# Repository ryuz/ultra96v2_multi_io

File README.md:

# Ultra96V2用マルチI/O拡張カード

現在デバッグ中ですが、MIPI-CSI の動作確認できました。

## 開発イメージ

下記のようなイメージで開発している [Ultra96V2](https://www.avnet.com/wps/portal/japan/products/product-highlights/ultra96/) 向けのI/O拡張ボードです。

## 設計コンセプト

コンセプトは

- [FusionPCB](https://www.fusionpcb.jp)さんの$4.9基板で作る
- [ZYBO](https://reference.digilentinc.com/reference/programmable-logic/zybo-z7/start) の良さ(PLのI/O機能の充実)の追加
- [Raspberry PI](https://ja.wikipedia.org/wiki/Raspberry_Pi) の良さ(PSのI/O機能の充実)の追加
- 使いたい機能だけ部品実装すれば最低限のコストで使える

です。

## 機能

主な機能として

- PLの機能
    - TXS0108で3.3V双方向変換した12pin PMOD × 2個
    - RaspberryPI互換 MIPI-CSIコネクタ× 2個
    - LED × 4個
    - プッシュスイッチ × 2個 
    - ディップスイッチ(4bit) × 1個 
    - 25MHzクロック供給
- PSの機能
    - LED × 2個
    - TXS0108で3.3V双方向変換したGPIO
    - TXS0108で3.3V双方向変換したI2C
    - TXS0108で3.3V双方向変換したSPI
- その他の機能
    - 隠れると困るPWR/RSTスイッチの引き出し
    - 申し訳程度にUSB2.0信号を引き出したピンヘッダ

特に MIPI-CSI は、[こちら](http://nahitafu.cocolog-nifty.com/nahitafu/2008/11/post-57a1.html)を参考にさせて頂いて、基板厚 0.6mm の想定で設計時の机上計算のみ行っています)。

## 回路図

回路図は[こちら](documents/ultra96v2_multi_io_schematic.pdf)

## 追加情報

こちらに[ブログ記事](https://ryuz.hatenablog.com/entry/2020/07/26/215500)を書きました。

## 修正履歴

- Rev.1 2020/02/11
   - 修正内容
       - 初版
   - 動作状況
       - MIPI-CSI が同パターンの別基板でデータ受信でき無かったため、部品温存で試さずに Rev.2 製造へ

- Rev.2 2020/03/08
   - 修正内容
       - MIPI 配線レイアウト変更
       - 基板厚を 0.6mm に変更して発注
   - 動作状況
       - J3のMIPI-CSI動作確認(I2Cプルアップをリワーク修正)
       - J4のMIPI-CSI動作確認(I2Cプルアップをリワーク修正)
       - PMODの出力パルス波形確認
       - SW5(DIP-SW)の型番とフットプリントが不一致で実装できず
       - MIPI-DSIの端子をLVCMOS利用箇所でLVCMOS18と勘違いしておりLED点灯が暗い(実際はLVCMOS12)
       - 他はこれから試す予定

- Rev.3 2023/02/15
   - MIPI-CSI用 I2C プルアップ抵抗抜け修正(R23～26追加)
   - LS_GPIO_2 と LS_GPIO_6 の U4 への接続をスワップ
   - Q1-4 の DMN63D8LDW-7 -> DMN5L0-6DWK7 に変更(LVCMOS12対応)
   - SW5 の GDH04S04 のフットプリントが A6H-4101 用になっていたので両対応パターンに変更
   - fumi氏に HSコネクタに来ている信号のうち Bank65 に繋がるものがは 1.2V だと指摘頂き下記を修正
       - SW1, SW2, SW5 を FPGA内部PULLUPして論理逆で使う方針に変更(R35, R36, R31, R32, R33, R34 削除)
       - U3 を使わずにそのままピンヘッダへ (U3, C8, C10, R11, R12 削除)
       - KiCAD を 7.0.0 へ更新

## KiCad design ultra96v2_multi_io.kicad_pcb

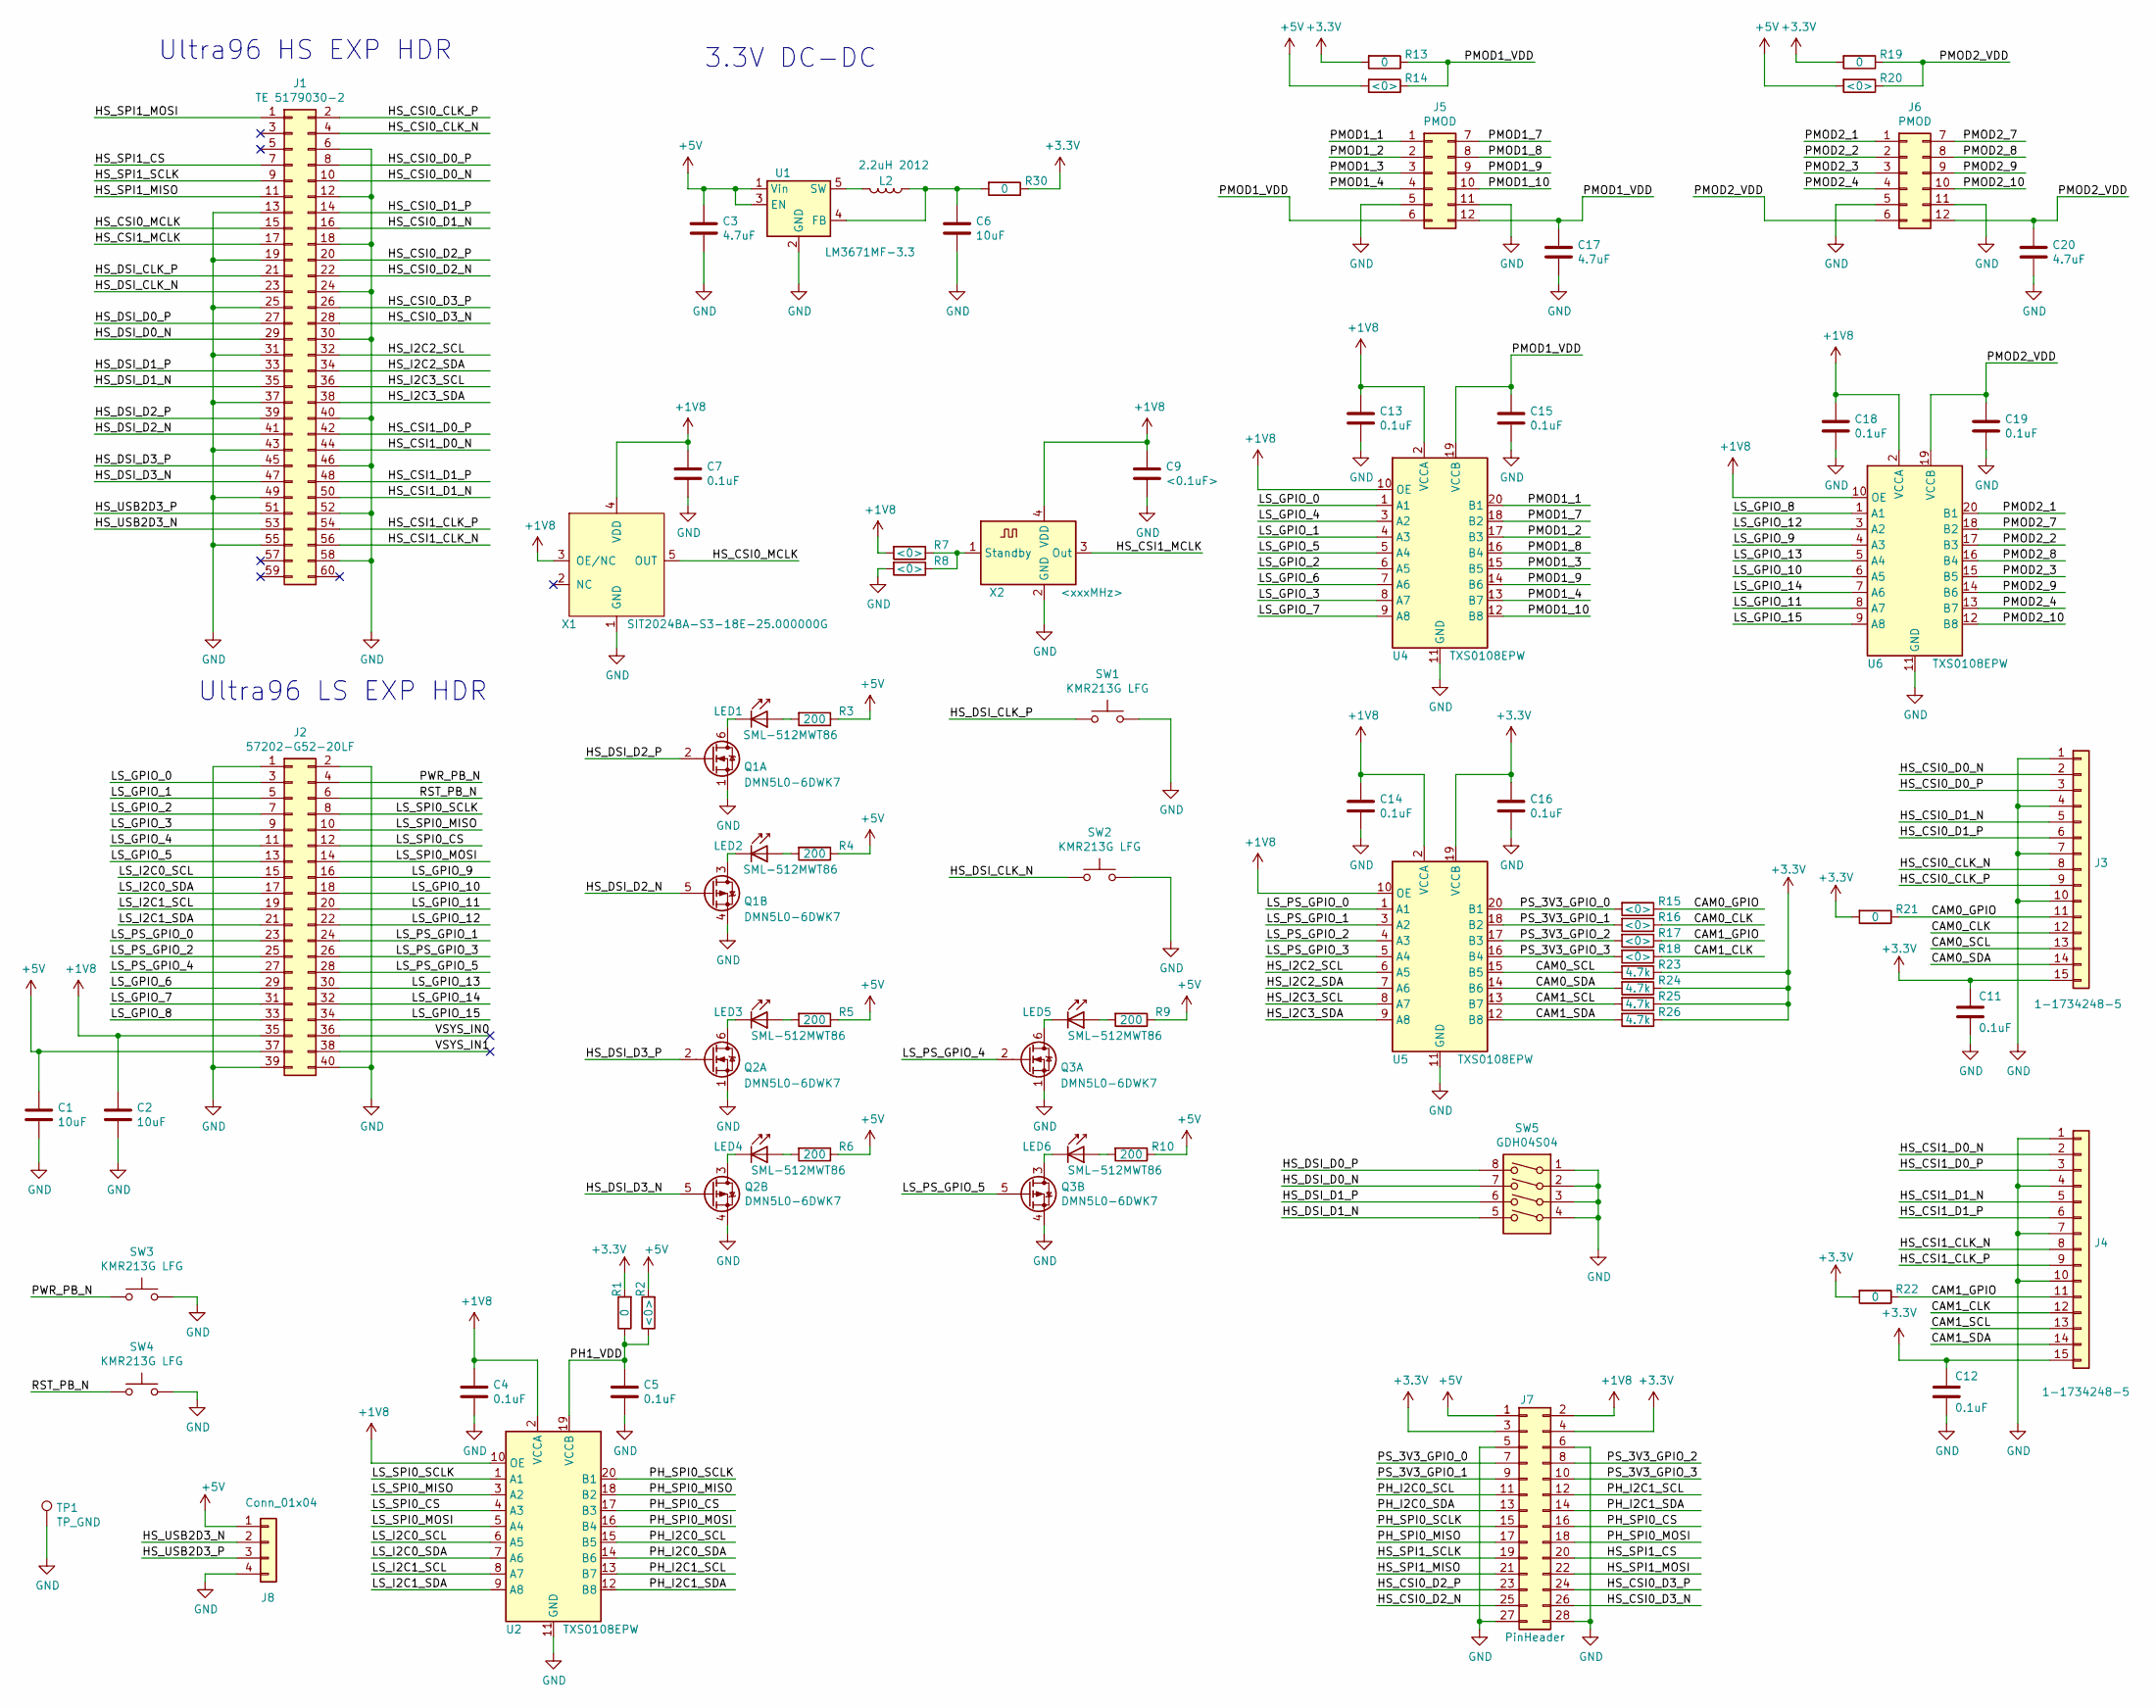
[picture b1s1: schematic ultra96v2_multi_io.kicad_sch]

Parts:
C1, C2, C6: 10uF; C_0603_1608Metric_Pad1.05x0.95mm_HandSolder
C3, C17, C20: 4.7uF; C_0603_1608Metric_Pad1.05x0.95mm_HandSolder
C4, C5, C7, C11, C12, C13, C14, C15, C16, C18, C19: 0.1uF; C_0603_1608Metric_Pad1.05x0.95mm_HandSolder
C9: <0.1uF>; C_0603_1608Metric_Pad1.05x0.95mm_HandSolder
J1: TE 5179030-2; 61083-063402LF
J2: 57202-G52-20LF; PinHeader_2x20_P2.00mm_Vertical_SMD_REV
J3, J4: 1-1734248-5; 55510-140LF_handsolder
J5, J6: PMOD; PMOD_Master
J7: PinHeader; PinHeader_2x14_P2.54mm_Vertical
J8: Conn_01x04; PinHeader_1x04_P2.54mm_Vertical
L2: 2.2uH 2012; L_0805_2012Metric
LED1, LED2, LED3, LED4, LED5, LED6: SML-512MWT86; LED_0603_1608Metric_Pad1.05x0.95mm_HandSolder
Q1, Q2, Q3: DMN5L0-6DWK7; SOT-363_SC-70-6_Handsoldering
R1, R13, R19, R21, R22, R30: 0; R_0603_1608Metric
R2, R7, R8, R14, R15, R16, R17, R18, R20: <0>; R_0603_1608Metric
R3, R4, R5, R6, R9, R10: 200; R_0603_1608Metric
R23, R24, R25, R26: 4.7k; R_0603_1608Metric
SW1, SW2, SW3, SW4: KMR213G LFG; SW_Push_1P1T_NO_CK_KMR2
SW5: GDH04S04; SW_DIP_multi_io
TP1: TP_GND; TestPoint_Loop_D1.80mm_Drill1.0mm_Beaded
U1: LM3671MF-3.3; TSOT-23-5
U2, U4, U5, U6: TXS0108EPW; TSSOP-20_4.4x6.5mm_P0.65mm
X1: SIT2024BA-S3-18E-25.000000G; SOT-23-5_HandSoldering
X2: <xxxMHz>; Oscillator_SMD_Abracon_ASDMB-4Pin_2.5x2.0mm

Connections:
+1V8: C2.1, C4.1, C7.1, C9.1, C13.1, C14.1, C18.1, J2.35, J7.2, R7.2, U2.2 (VCCA), U2.10 (OE), U4.2 (VCCA), U4.10 (OE), U5.2 (VCCA), U5.10 (OE), U6.2 (VCCA), U6.10 (OE), X1.3 (OE/NC), X1.4 (VDD), X2.4 (VDD)
+3V3: C11.1, C12.1, C16.1, J3.15, J4.15, J7.3, J7.4, R1.2, R13.2, R19.2, R21.2, R22.2, R23.1, R24.1, R25.1, R26.1, R30.1, U5.19 (VCCB)
+5V: C1.1, C3.1, J2.37, J7.1, J8.1, R2.2, R3.1, R4.1, R5.1, R6.1, R9.1, R10.1, R14.2, R20.2, U1.1 (Vin), U1.3 (EN)
/CAM0_CLK: J3.12, R16.1
/CAM0_GPIO: J3.11, R15.1, R21.1
/CAM0_SCL: J3.13, R23.2, U5.15 (B5)
/CAM0_SDA: J3.14, R24.2, U5.14 (B6)
/CAM1_CLK: J4.12, R18.1
/CAM1_GPIO: J4.11, R17.1, R22.1
/CAM1_SCL: J4.13, R25.2, U5.13 (B7)
/CAM1_SDA: J4.14, R26.2, U5.12 (B8)
/HS_CSI0_CLK_N: J1.4, J3.8
/HS_CSI0_CLK_P: J1.2, J3.9
/HS_CSI0_D0_N: J1.10, J3.2
/HS_CSI0_D0_P: J1.8, J3.3
/HS_CSI0_D1_N: J1.16, J3.5
/HS_CSI0_D1_P: J1.14, J3.6
/HS_CSI0_D2_N: J1.22, J7.25
/HS_CSI0_D2_P: J1.20, J7.23
/HS_CSI0_D3_N: J1.28, J7.26
/HS_CSI0_D3_P: J1.26, J7.24
/HS_CSI0_MCLK: J1.15, X1.5 (OUT)
/HS_CSI1_CLK_N: J1.56, J4.8
/HS_CSI1_CLK_P: J1.54, J4.9
/HS_CSI1_D0_N: J1.44, J4.2
/HS_CSI1_D0_P: J1.42, J4.3
/HS_CSI1_D1_N: J1.50, J4.5
/HS_CSI1_D1_P: J1.48, J4.6
/HS_CSI1_MCLK: J1.17, X2.3 (Out)
/HS_DSI_CLK_N: J1.23, SW2.1
/HS_DSI_CLK_P: J1.21, SW1.1
/HS_DSI_D0_N: J1.29, SW5.7
/HS_DSI_D0_P: J1.27, SW5.8
/HS_DSI_D1_N: J1.35, SW5.5
/HS_DSI_D1_P: J1.33, SW5.6
/HS_DSI_D2_N: J1.41, Q1.5 (G2)
/HS_DSI_D2_P: J1.39, Q1.2 (G1)
/HS_DSI_D3_N: J1.47, Q2.5 (G2)
/HS_DSI_D3_P: J1.45, Q2.2 (G1)
/HS_I2C2_SCL: J1.32, U5.6 (A5)
/HS_I2C2_SDA: J1.34, U5.7 (A6)
/HS_I2C3_SCL: J1.36, U5.8 (A7)
/HS_I2C3_SDA: J1.38, U5.9 (A8)
/HS_SPI1_CS: J1.7, J7.20
/HS_SPI1_MISO: J1.11, J7.21
/HS_SPI1_MOSI: J1.1, J7.22
/HS_SPI1_SCLK: J1.9, J7.19
/HS_USB2D3_N: J1.53, J8.2
/HS_USB2D3_P: J1.51, J8.3
/LS_GPIO_0: J2.3, U4.1 (A1)
/LS_GPIO_1: J2.5, U4.4 (A3)
/LS_GPIO_2: J2.7, U4.6 (A5)
/LS_GPIO_3: J2.9, U4.8 (A7)
/LS_GPIO_4: J2.11, U4.3 (A2)
/LS_GPIO_5: J2.13, U4.5 (A4)
/LS_GPIO_6: J2.29, U4.7 (A6)
/LS_GPIO_7: J2.31, U4.9 (A8)
/LS_GPIO_8: J2.33, U6.1 (A1)
/LS_GPIO_9: J2.16, U6.4 (A3)
/LS_GPIO_10: J2.18, U6.6 (A5)
/LS_GPIO_11: J2.20, U6.8 (A7)
/LS_GPIO_12: J2.22, U6.3 (A2)
/LS_GPIO_13: J2.30, U6.5 (A4)
/LS_GPIO_14: J2.32, U6.7 (A6)
/LS_GPIO_15: J2.34, U6.9 (A8)
/LS_I2C0_SCL: J2.15, U2.6 (A5)
/LS_I2C0_SDA: J2.17, U2.7 (A6)
/LS_I2C1_SCL: J2.19, U2.8 (A7)
/LS_I2C1_SDA: J2.21, U2.9 (A8)
/LS_PS_GPIO_0: J2.23, U5.1 (A1)
/LS_PS_GPIO_1: J2.24, U5.3 (A2)
/LS_PS_GPIO_2: J2.25, U5.4 (A3)
/LS_PS_GPIO_3: J2.26, U5.5 (A4)
/LS_PS_GPIO_4: J2.27, Q3.2 (G1)
/LS_PS_GPIO_5: J2.28, Q3.5 (G2)
/LS_SPI0_CS: J2.12, U2.4 (A3)
/LS_SPI0_MISO: J2.10, U2.3 (A2)
/LS_SPI0_MOSI: J2.14, U2.5 (A4)
/LS_SPI0_SCLK: J2.8, U2.1 (A1)
/PH1_VDD: C5.1, R1.1, R2.1, U2.19 (VCCB)
/PH_I2C0_SCL: J7.11, U2.15 (B5)
/PH_I2C0_SDA: J7.13, U2.14 (B6)
/PH_I2C1_SCL: J7.12, U2.13 (B7)
/PH_I2C1_SDA: J7.14, U2.12 (B8)
/PH_SPI0_CS: J7.16, U2.17 (B3)
/PH_SPI0_MISO: J7.17, U2.18 (B2)
/PH_SPI0_MOSI: J7.18, U2.16 (B4)
/PH_SPI0_SCLK: J7.15, U2.20 (B1)
/PMOD1_1: J5.1, U4.20 (B1)
/PMOD1_2: J5.2, U4.17 (B3)
/PMOD1_3: J5.3, U4.15 (B5)
/PMOD1_4: J5.4, U4.13 (B7)
/PMOD1_7: J5.7, U4.18 (B2)
/PMOD1_8: J5.8, U4.16 (B4)
/PMOD1_9: J5.9, U4.14 (B6)
/PMOD1_10: J5.10, U4.12 (B8)
/PMOD1_VDD: C15.1, C17.1, J5.6, J5.12, R13.1, R14.1, U4.19 (VCCB)
/PMOD2_1: J6.1, U6.20 (B1)
/PMOD2_2: J6.2, U6.17 (B3)
/PMOD2_3: J6.3, U6.15 (B5)
/PMOD2_4: J6.4, U6.13 (B7)
/PMOD2_7: J6.7, U6.18 (B2)
/PMOD2_8: J6.8, U6.16 (B4)
/PMOD2_9: J6.9, U6.14 (B6)
/PMOD2_10: J6.10, U6.12 (B8)
/PMOD2_VDD: C19.1, C20.1, J6.6, J6.12, R19.1, R20.1, U6.19 (VCCB)
/PS_3V3_GPIO_0: J7.7, R15.2, U5.20 (B1)
/PS_3V3_GPIO_1: J7.9, R16.2, U5.18 (B2)
/PS_3V3_GPIO_2: J7.8, R17.2, U5.17 (B3)
/PS_3V3_GPIO_3: J7.10, R18.2, U5.16 (B4)
/PWR_PB_N: J2.4, SW3.1
/RST_PB_N: J2.6, SW4.1
/VSYS_IN0: J2.36
/VSYS_IN1: J2.38
GND: C1.2, C2.2, C3.2, C4.2, C5.2, C6.2, C7.2, C9.2, C11.2, C12.2, C13.2, C14.2, C15.2, C16.2, C17.2, C18.2, C19.2, C20.2, J1.6, J1.12, J1.13, J1.18, J1.19, J1.24, J1.25, J1.30, J1.31, J1.37, J1.40, J1.43, J1.46, J1.49, J1.52, J1.55, J1.58, J2.1, J2.2, J2.39, J2.40, J3.1, J3.4, J3.7, J3.10, J4.1, J4.4, J4.7, J4.10, J5.5, J5.11, J6.5, J6.11, J7.5, J7.6, J7.27, J7.28, J8.4, Q1.1 (S1), Q1.4 (S2), Q2.1 (S1), Q2.4 (S2), Q3.1 (S1), Q3.4 (S2), R8.2, SW1.2, SW2.2, SW3.2, SW4.2, SW5.1, SW5.2, SW5.3, SW5.4, TP1.1, U1.2 (GND), U2.11 (GND), U4.11 (GND), U5.11 (GND), U6.11 (GND), X1.1 (GND), X2.2 (GND)
unnamed: LED1.2 (A), R3.2
unnamed: LED1.1 (K), Q1.6 (D1)
unnamed: LED2.2 (A), R4.2
unnamed: LED2.1 (K), Q1.3 (D2)
unnamed: LED3.2 (A), R5.2
unnamed: LED3.1 (K), Q2.6 (D1)
unnamed: LED4.2 (A), R6.2
unnamed: LED4.1 (K), Q2.3 (D2)
unnamed: LED5.2 (A), R9.2
unnamed: LED5.1 (K), Q3.6 (D1)
unnamed: LED6.2 (A), R10.2
unnamed: LED6.1 (K), Q3.3 (D2)
unnamed: C6.1, L2.1, R30.2, U1.4 (FB)
unnamed: L2.2, U1.5 (SW)
unnamed: R7.1, R8.1, X2.1 (Standby)

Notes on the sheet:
Ultra96 LS EXP HDR
3.3V DC-DC
Ultra96 HS EXP HDR

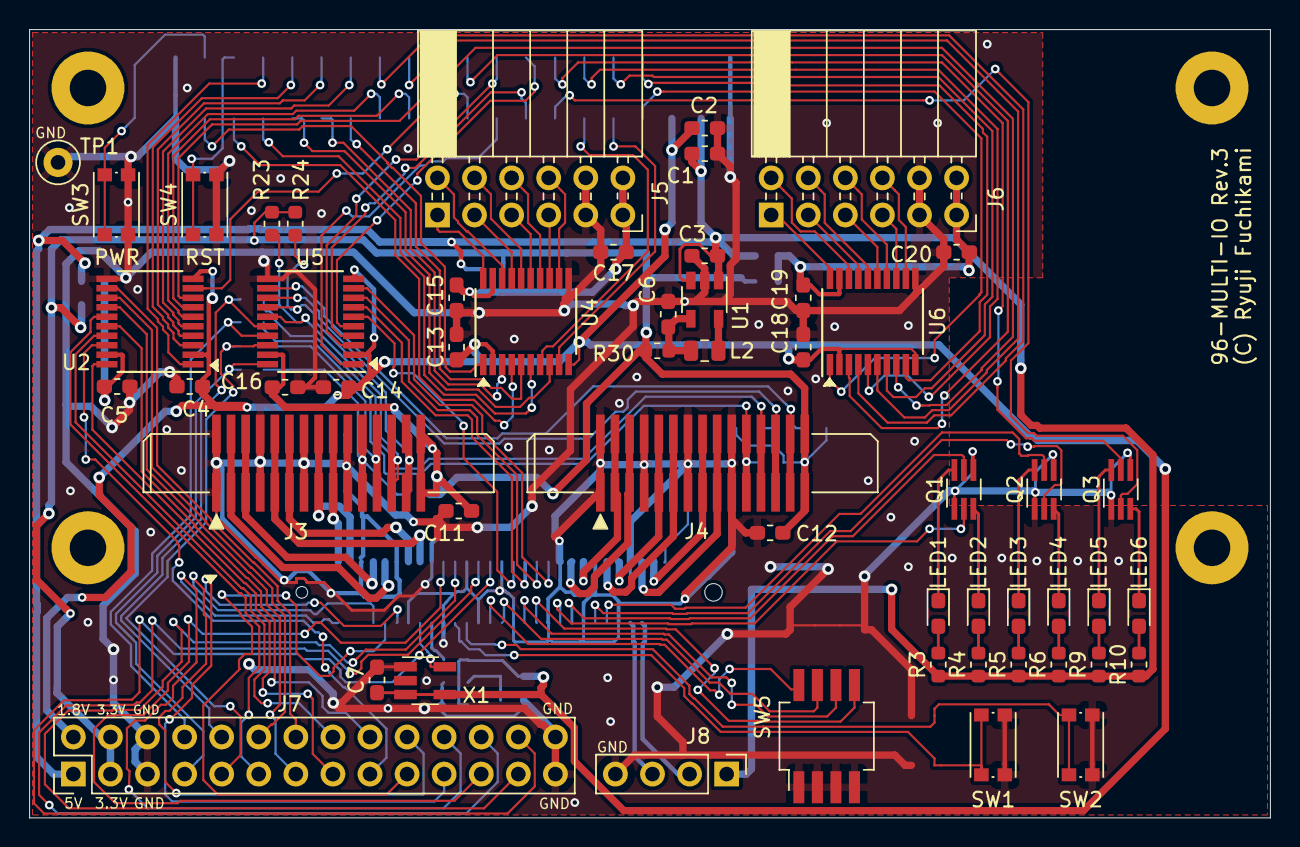
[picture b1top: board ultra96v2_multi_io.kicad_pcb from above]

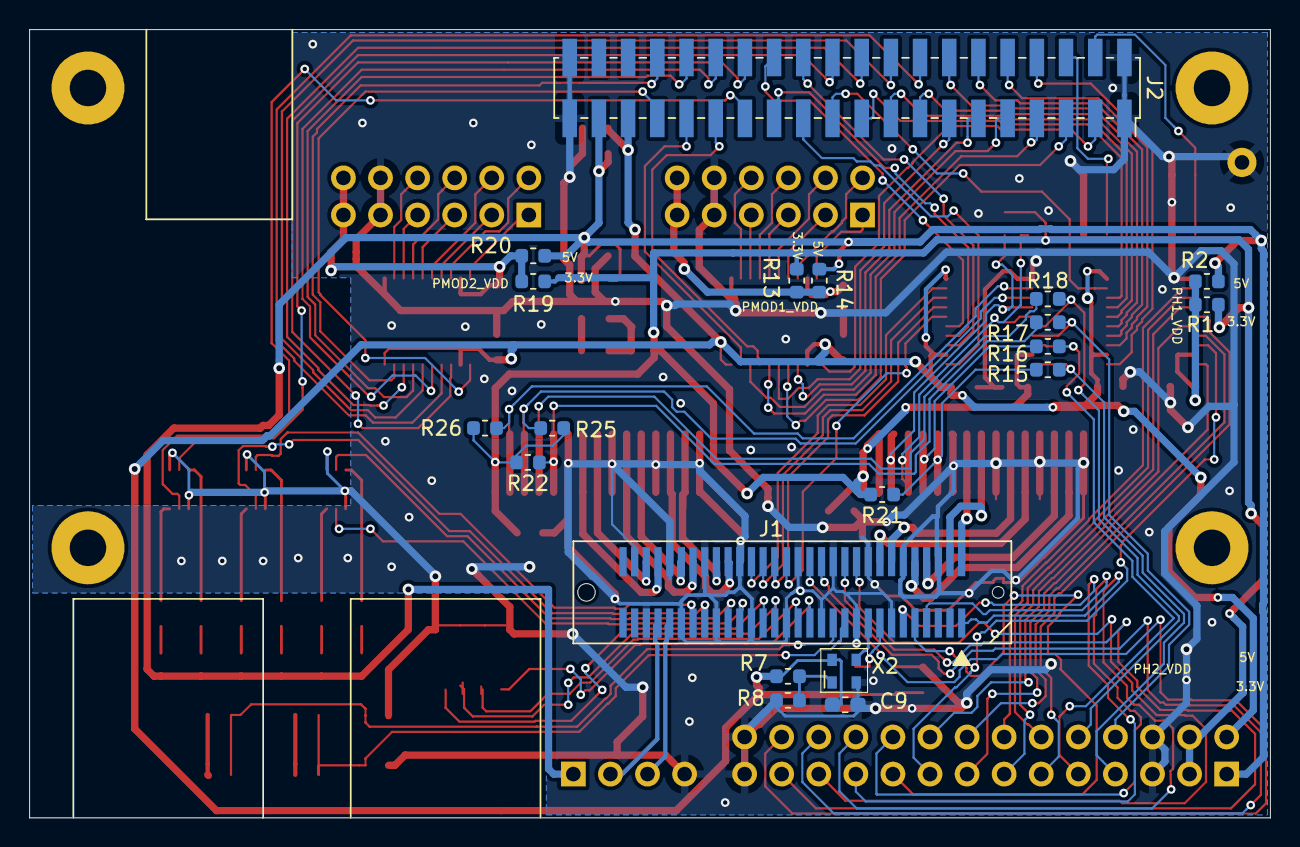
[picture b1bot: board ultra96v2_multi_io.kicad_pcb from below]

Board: 2 copper layers, 85.0 x 54.0 mm, 74 parts (20 on the bottom side), 128 nets.

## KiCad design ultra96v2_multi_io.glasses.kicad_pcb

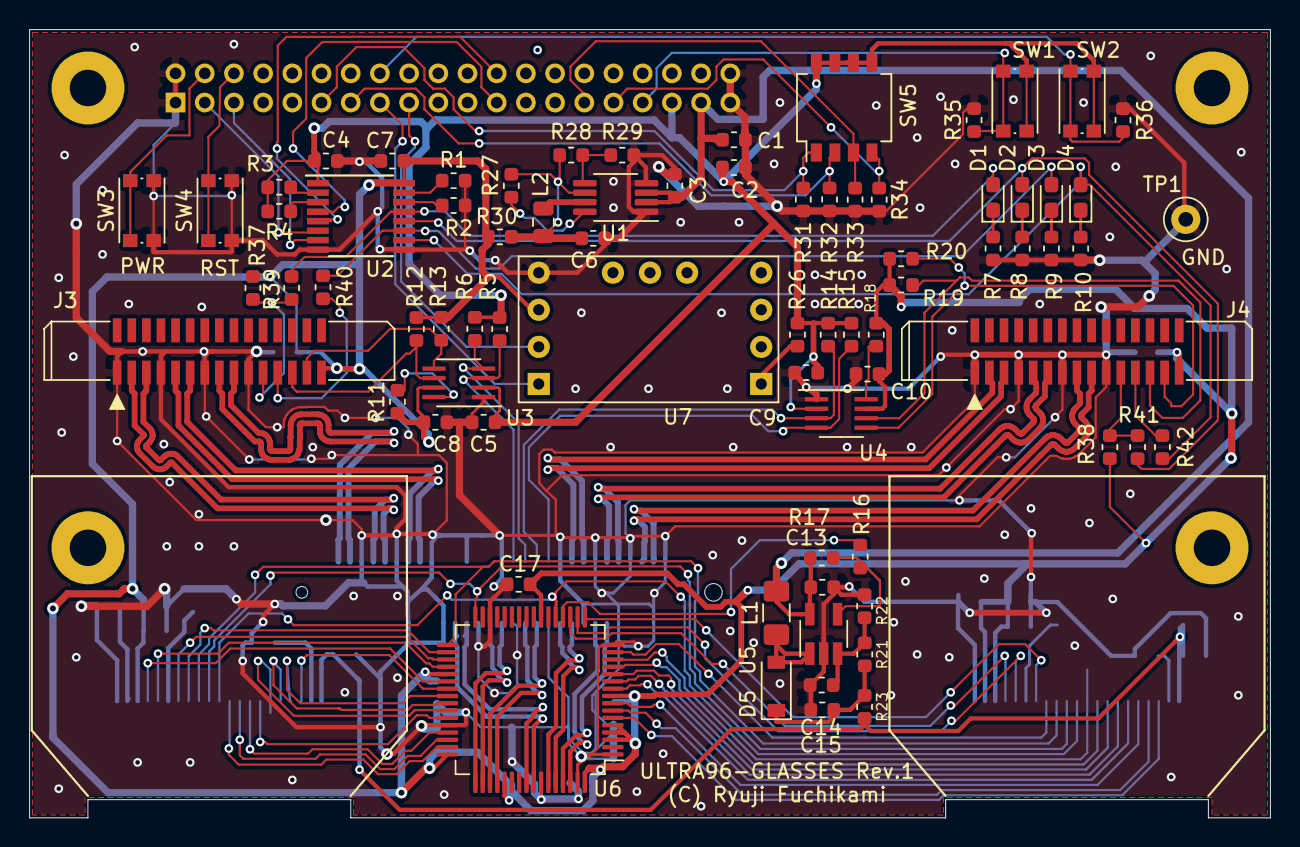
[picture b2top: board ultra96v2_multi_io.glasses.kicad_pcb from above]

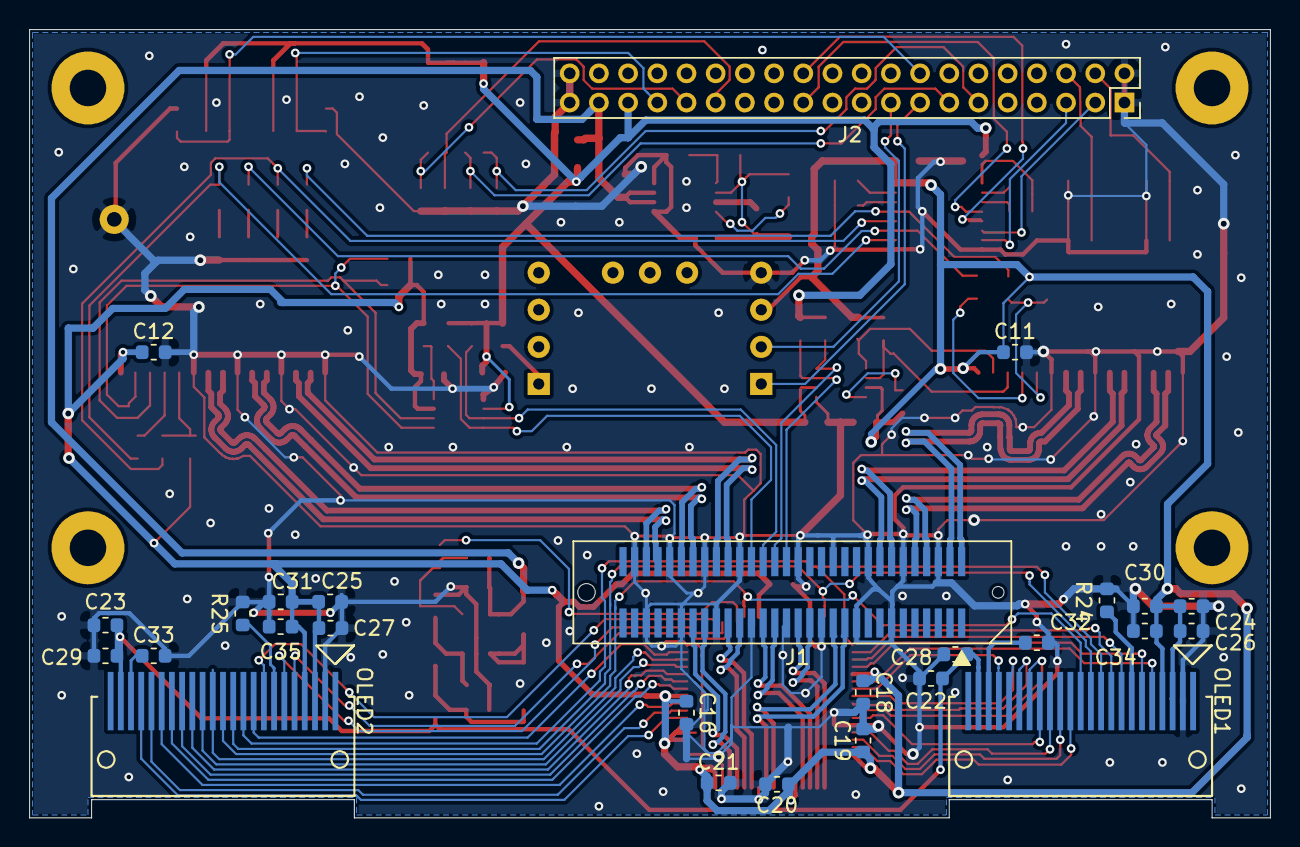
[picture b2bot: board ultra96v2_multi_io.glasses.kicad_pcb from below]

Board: 2 copper layers, 85.0 x 54.0 mm, 103 parts (27 on the bottom side), 108 nets.

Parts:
C1, C2, C3: 10uF; C_0603_1608Metric
C4, C5, C7, C8, C9, C10, C11, C12, C16, C17, C18, C19, C20, C21, C26, C27, C34, C35: 0.1uF; C_0603_1608Metric
C6: 22uF; C_0603_1608Metric
C13: 2.2uF; C_0603_1608Metric
C14: 220pF/25V; C_0603_1608Metric
C15, C32, C33: 4.7uF 25V; C_0603_1608Metric
C22, C23: 10uF 25V; C_0603_1608Metric
C24, C25, C30, C31: 4.7uF; C_0603_1608Metric
C28, C29: 0.1uF 25V; C_0603_1608Metric
D1, D2, D3, D4: SML-512MWT86; LED_0603_1608Metric_Pad1.05x0.95mm_HandSolder
D5: MBR0520LT1G; D_SOD-123
J1: 61083-063402LF
J2: 10075024-G01-20ULF; PinSocket_2x20_P2.00mm_Vertical
J3, J4: 1-1734248-5; 55510-140LF
L1: 10uH CBC2518T100M; L_1206_3216Metric_Pad1.42x1.75mm_HandSolder
L2: 2.2uH MLZ2012A2R2MT; L_0805_2012Metric
OLED1, OLED2: UG-9664HDDAG01
R1, R2, R3, R4, R11, R16, R18, R23, R26, R30, R37, R38: 0; R_0603_1608Metric
R5, R6, R12, R13, R14, R15, R19, R20, R31, R32, R33, R34, R35, R36: 4.7k; R_0603_1608Metric
R7, R8, R9, R10: 10; R_0603_1608Metric
R17: 51k; R_0603_1608Metric
R21: 140k; R_0603_1608Metric
R22: 13.3k; R_0603_1608Metric
R24, R25: 1.1M; R_0603_1608Metric
R27: 100k; R_0603_1608Metric
R28: 562k; R_0603_1608Metric
R29: 180k; R_0603_1608Metric
R39, R40, R41, R42: <0>; R_0603_1608Metric
SW1, SW2, SW3, SW4: KMR213G LFG; SW_Push_1P1T_NO_CK_KMR2
SW5: GDH04S04; SW_DIP_SPSTx04_Slide_Omron_A6H-4101_W6.15mm_P1.27mm
TP1: TP_GND; TestPoint_Loop_D1.80mm_Drill1.0mm_Beaded
U1: TPS62160DGK
U2: SN74AVC4T245PW; TSSOP-16_4.4x5mm_P0.65mm
U3, U4: PCA9306DCTR
U5: LM2733XMF; SOT-23-5_HandSoldering
U6: BU90R104; TQFP-64_10x10mm_P0.5mm
U7: SS-MPU-9250

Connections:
+1V8: C2.1, C4.1, C5.1, C9.1, J2.35, R3.2, R4.2, R5.2, R6.2, R14.2, R15.2, R26.2, SW1.2, SW2.2, SW5.5, SW5.6, SW5.7, SW5.8, U2.1, U3.2, U4.2
+3V3: C7.1, C8.1, C10.1, C11.1, C12.1, C16.1, C17.1, C18.1, C19.1, C20.1, C21.1, C24.1, C25.1, C26.1, C27.1, C30.1, C31.1, C34.1, C35.1, J3.15, J4.15, OLED1.3, OLED1.4, OLED2.3, OLED2.4, R11.1, R12.1, R13.1, R18.1, R19.1, R20.1, R30.1, R37.2, R38.2, U2.16, U3.7, U4.7, U6.3, U6.4, U6.5, U6.9, U6.23, U6.37, U6.48, U6.53, U6.64, U7.J1-3
+5V: C1.1, C3.1, C13.1, J2.37, L1.2, R17.1, U1.2, U1.3, U5.5
/CAM0_CLK: J3.12, R40.1
/CAM0_GPIO: J3.11, R37.1, R39.1
/CAM0_SCL: J3.13, R12.2, U3.6
/CAM0_SDA: J3.14, R13.2, U3.5
/CAM1_CLK: J4.12, R42.1
/CAM1_GPIO: J4.11, R38.1, R41.1
/CAM1_SCL: J4.13, R19.2, U4.6
/CAM1_SDA: J4.14, R20.2, U4.5
/HS_CSI0_CLK_N: J1.4, J3.8
/HS_CSI0_CLK_P: J1.2, J3.9
/HS_CSI0_D0_N: J1.10, J3.2
/HS_CSI0_D0_P: J1.8, J3.3
/HS_CSI0_D1_N: J1.16, J3.5
/HS_CSI0_D1_P: J1.14, J3.6
/HS_CSI1_CLK_N: J1.56, J4.8
/HS_CSI1_CLK_P: J1.54, J4.9
/HS_CSI1_D0_N: J1.44, J4.2
/HS_CSI1_D0_P: J1.42, J4.3
/HS_CSI1_D1_N: J1.50, J4.5
/HS_CSI1_D1_P: J1.48, J4.6
/HS_DSI_CLK_N: J1.23, U6.56
/HS_DSI_CLK_P: J1.21, U6.57
/HS_DSI_D0_N: J1.29, U6.49
/HS_DSI_D0_P: J1.27, U6.50
/HS_DSI_D1_N: J1.35, U6.51
/HS_DSI_D1_P: J1.33, U6.52
/HS_DSI_D2_N: J1.41, U6.59
/HS_DSI_D2_P: J1.39, U6.60
/HS_DSI_D3_N: J1.47, U6.61
/HS_DSI_D3_P: J1.45, U6.62
/HS_I2C2_SCL: J1.32, R5.1, U3.3
/HS_I2C2_SDA: J1.34, R6.1, U3.4
/HS_I2C3_SCL: J1.36, R14.1, U4.3
/HS_I2C3_SDA: J1.38, R15.1, U4.4
/LS_3V3_GPIO_0: D3.2, R40.2, U2.11
/LS_3V3_GPIO_1: D4.2, R42.2, U2.10
/LS_3V3_PS_GPIO_0: D1.2, R39.2, U2.13
/LS_3V3_PS_GPIO_1: D2.2, R41.2, U2.12
/LS_GPIO_0: J2.3, U2.6
/LS_GPIO_1: J2.5, U2.7
/LS_GPIO_4: J2.11, R31.1, SW5.1
/LS_GPIO_5: J2.13, R32.1, SW5.2
/LS_GPIO_6: J2.29, R33.1, SW5.3
/LS_GPIO_7: J2.31, R34.1, SW5.4
/LS_GPIO_8: J2.33, R35.1, SW1.1
/LS_GPIO_9: J2.16, R36.1, SW2.1
/LS_I2C0_SCL: J2.15, U7.J1-1
/LS_I2C0_SDA: J2.17, U7.J1-2
/LS_PS_GPIO_0: J2.23, U2.4
/LS_PS_GPIO_1: J2.24, U2.5
/OLED0_BS1: OLED1.5, U6.38
/OLED0_BS2: OLED1.6, U6.36
/OLED0_CS: OLED1.8, U6.35
/OLED0_D0: OLED1.13, U6.47
/OLED0_D1: OLED1.14, U6.46
/OLED0_D2: OLED1.15, U6.45
/OLED0_D3: OLED1.16, U6.43
/OLED0_D4: OLED1.17, U6.42
/OLED0_D5: OLED1.18, U6.41
/OLED0_D6: OLED1.19, U6.40
/OLED0_D7: OLED1.20, U6.39
/OLED0_IREF: OLED1.7, R24.2
/OLED0_RES: OLED1.9, U6.34
/OLED0_VCOMH: C32.1, OLED1.21
/OLED1_BS1: OLED2.5, U6.19
/OLED1_BS2: OLED2.6, U6.18
/OLED1_CS: OLED2.8, U6.17
/OLED1_D0: OLED2.13, U6.14
/OLED1_D1: OLED2.14, U6.13
/OLED1_D2: OLED2.15, U6.12
/OLED1_D3: OLED2.16, U6.11
/OLED1_D4: OLED2.17, U6.10
/OLED1_D5: OLED2.18, U6.8
/OLED1_D6: OLED2.19, U6.7
/OLED1_D7: OLED2.20, U6.6
/OLED1_IREF: OLED2.7, R25.2
/OLED1_RES: OLED2.9, U6.15
/OLED1_VCOMH: C33.1, OLED2.21
/OLED_DC: OLED1.10, OLED2.10, U6.33
/OLED_E: OLED1.12, OLED2.12, U6.21
/OLED_RW: OLED1.11, OLED2.11, U6.32
/PWR_EN: R16.1, U6.20
/PWR_PB_N: J2.4, SW3.1
/RST_PB_N: J2.6, SW4.1
/VCC_FB: C14.1, R21.2, R22.1, U5.3
/VCC_OUT: C15.1, D5.1, R21.1, R23.1
/VCC_SHDN: R16.2, R17.2, U5.4
/VCC_SW: D5.2, L1.1, U5.1
GND: C1.2, C2.2, C3.2, C4.2, C5.2, C6.2, C7.2, C8.2, C9.2, C10.2, C11.2, C12.2, C13.2, C14.2, C15.2, C16.2, C17.2, C18.2, C19.2, C20.2, C21.2, C22.2, C23.2, C24.2, C25.2, C26.2, C27.2, C28.2, C29.2, C30.2, C31.2, C32.2, C33.2, C34.2, C35.2, J1.6, J1.12, J1.13, J1.18, J1.19, J1.24, J1.25, J1.30, J1.31, J1.37, J1.40, J1.43, J1.46, J1.49, J1.52, J1.55, J1.58, J2.1, J2.2, J2.39, J2.40, J3.1, J3.4, J3.7, J3.10, J4.1, J4.4, J4.7, J4.10, OLED1.2, OLED2.2, R1.2, R2.2, R7.1, R8.1, R9.1, R10.1, R22.2, R24.1, R25.1, R29.1, R31.2, R32.2, R33.2, R34.2, R35.2, R36.2, SW3.2, SW4.2, TP1.1, U1.1, U1.4, U2.8, U2.9, U3.1, U4.1, U5.2, U6.1, U6.16, U6.30, U6.44, U6.58, U6.63, U7.J1-4
unnamed: C6.1, L2.1, R27.2, R28.2, R30.2, U1.6
unnamed: D1.1, R7.2
unnamed: D2.1, R8.2
unnamed: D3.1, R9.2
unnamed: D4.1, R10.2
unnamed: L2.2, U1.7
unnamed: R1.1, U2.15
unnamed: R2.1, U2.14
unnamed: R3.1, U2.2
unnamed: R4.1, U2.3
unnamed: R11.2, U3.8
unnamed: R18.2, U4.8
unnamed: R26.1, U7.J3-1
unnamed: R27.1, U1.8
unnamed: R28.1, R29.2, U1.5
VCC: C22.1, C23.1, C28.1, C29.1, OLED1.22, OLED2.22, R23.2

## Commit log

2020-03-08 rev2
2020-03-08 update rev2
2020-06-14 update document
2020-07-21 update to rev3 add MIPI-SCI I2C pullup register
2020-07-25 LS_GPIO_2 と LS_GPIO_6 の U4 への接続をスワップ
2020-07-26 Q1-4 の DMN63D8LDW-7 -> DMN5L0-6DWK7 に変更(LVCMOS12対応) SW5 の GDH04S04 のフットプリントが A6H-4101 用になっていたので両対応パターンに変更
2020-07-26 add SW_DIP_multi_io.kicad_mod
2021-05-14 update blog URL
2023-02-15 HSコネクタの 1.2V信号を誤って 1.8V として扱っていた点を修正。
    詳細はREADME参照の事
2023-02-18 未接続ネットの削除など
